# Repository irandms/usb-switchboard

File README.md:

# USB Switchboard Bonnet

This repository houses the KiCad design files for a Raspberry Pi Zero Bonnet
board. The system provides three independently controlled USB ports, which can
be selectively enabled or disabled for power delivery purposes via 3 GPIO pins
on the Pi host. The data pins for all receptacles are unused.

In addition to being able to digitally control each USB port, each port has
suppport for overcurrent protection via the [Texas Instruments TPS2556 IC](https://www.ti.com/product/TPS2556)
, capping out to ~500 mA per port. Fault/short circuit and temperature 
protection is also provided by the TPS2556.

When tested using an Pac-Man Silhouette LED Blue Ghost, it can provide PWM 
diming at ~500 Hz or faster depending on the period, with an untested upper
bound.

The initial set of prototype boards were made at [OSH Park](https://oshpark.com/shared_projects/6m9zgemo) using their 2oz Copper service, as the current through
the 5V input net from the Pi host could be fairly high depending on the
state of each of the ports and the devices connected to them.

bill-of-materials.csv contains a DigiKey-importable Bill of Materials that
has every component required on the PCB. Notably missing are the HAT EEPROM and
related passives, which can be found on the underside of the board.

The three channels can be enabled/disabled through the following GPIO pins:

| GPIO Pin      | Channel       |
| ------------- |:-------------:|
| GPIO2         | CH0           |
| GPIO10        | CH1           |
| GPIO11        | CH2           |

## NOTE:
I have not worked on including an EEPROM for this board to conform to the 
official Raspberry Pi Bonnet/HAT spec.

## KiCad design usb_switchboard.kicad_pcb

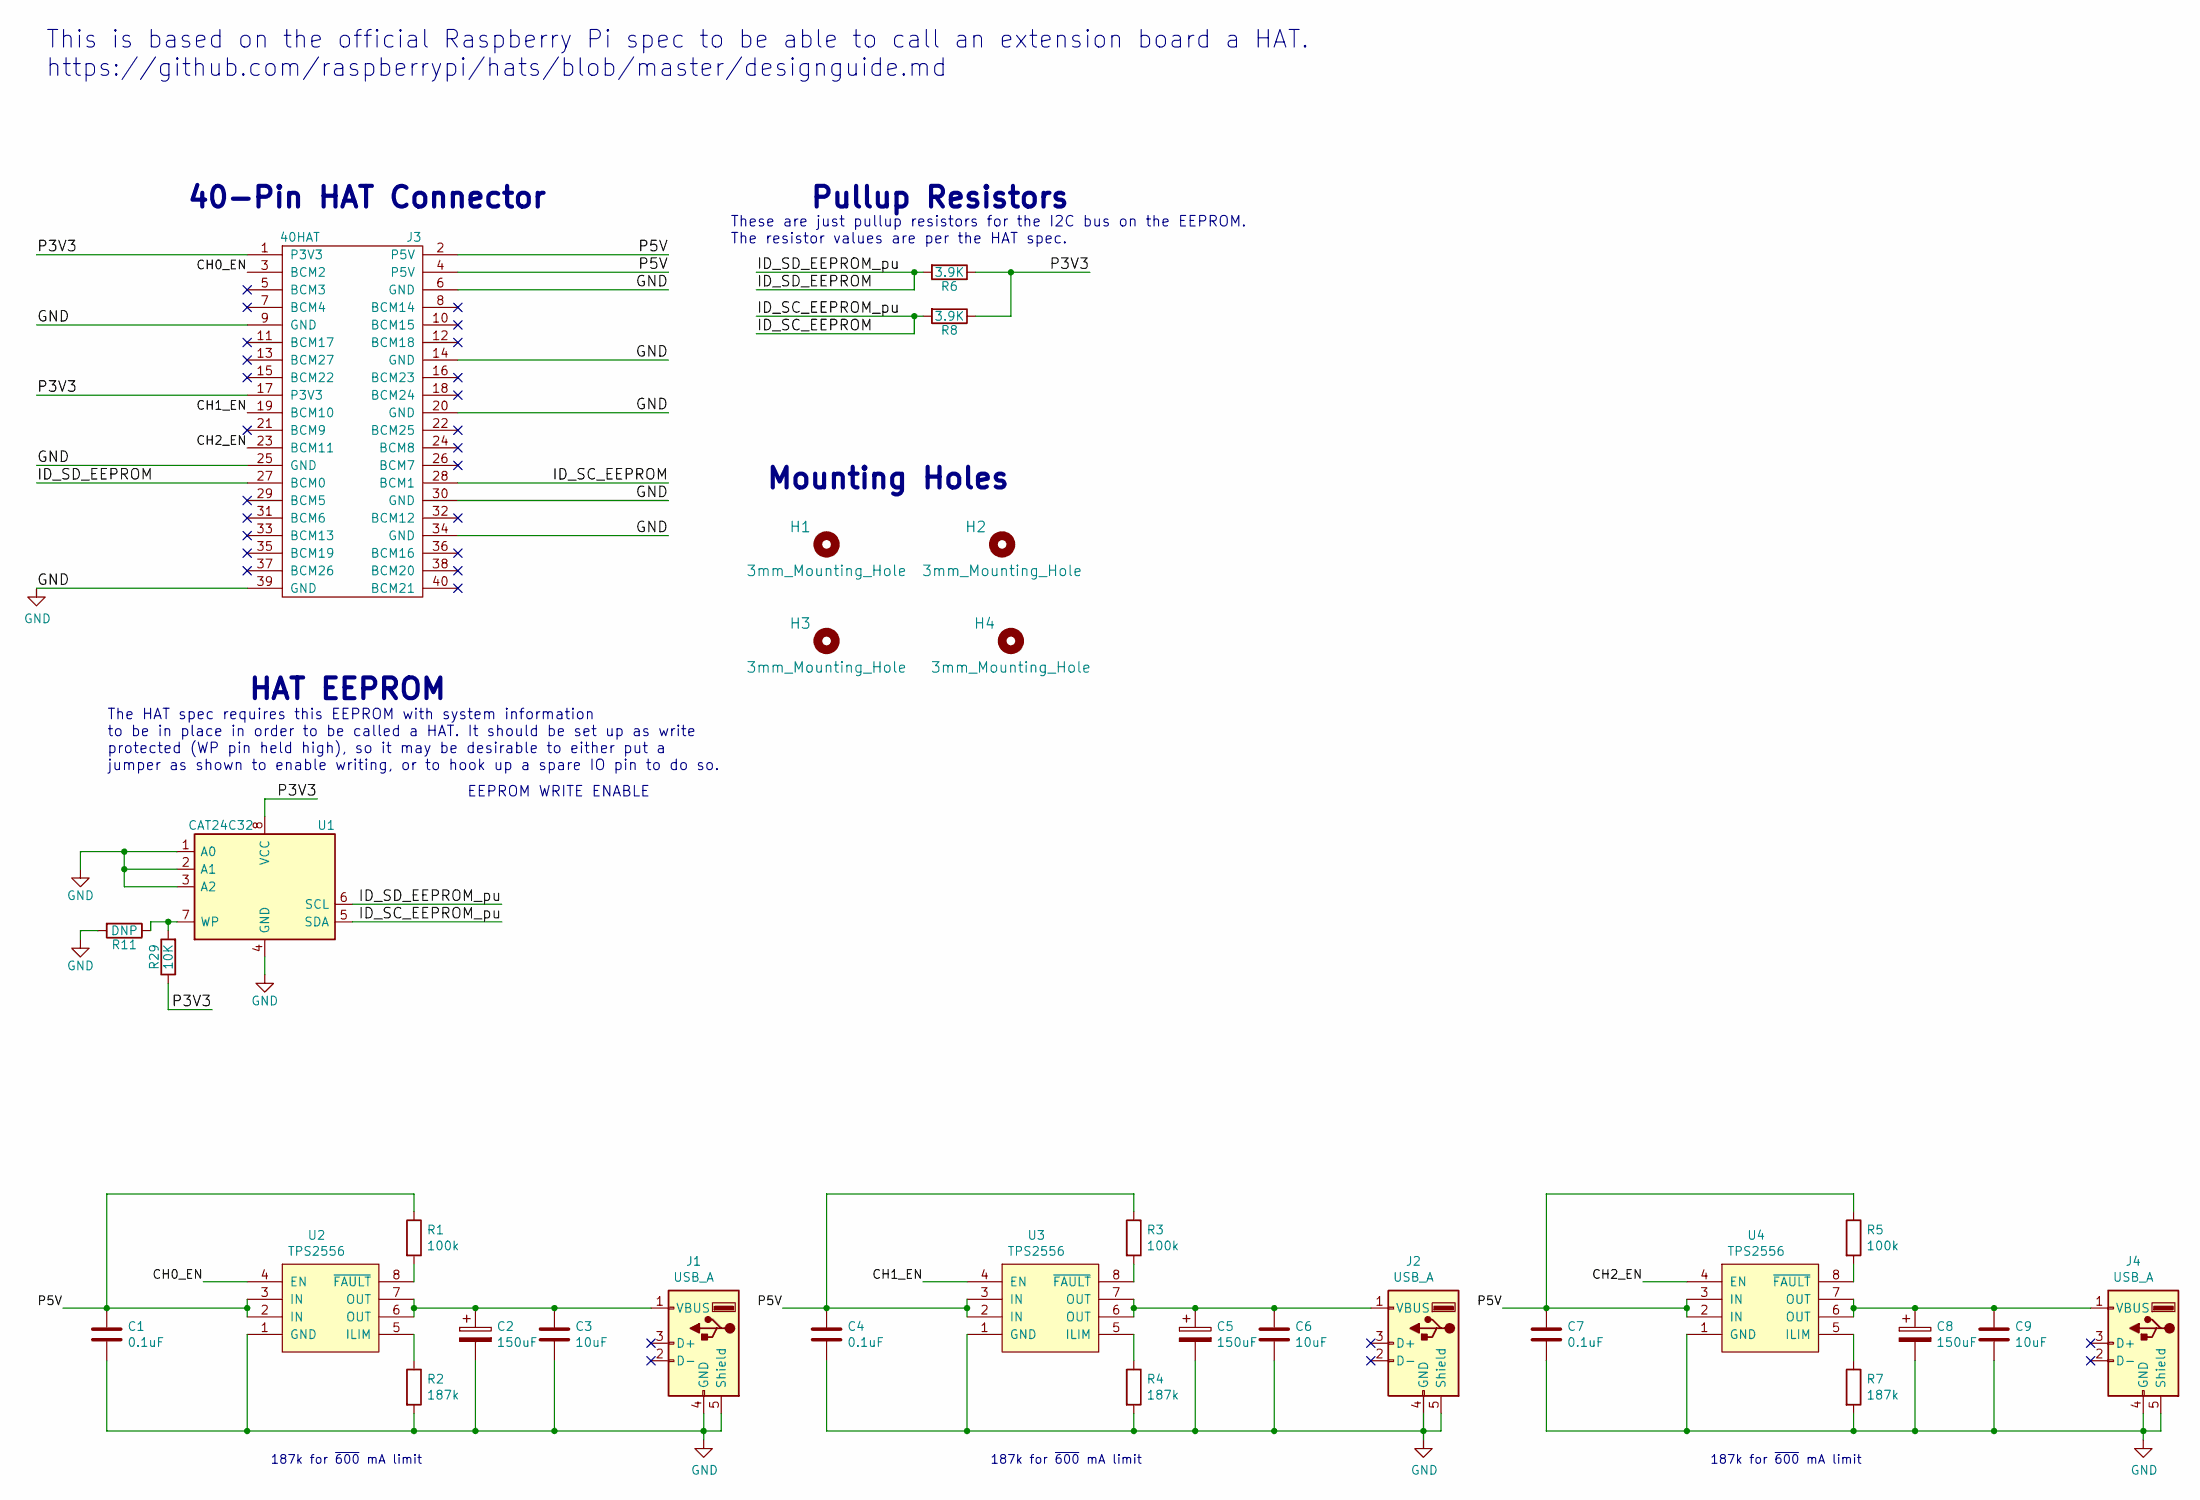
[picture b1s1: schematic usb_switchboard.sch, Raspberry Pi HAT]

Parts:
C1, C4, C7: 0.1uF; C_0603_1608Metric
C2, C5, C8: 150uF; CP_Elec_5x5.3
C3, C6, C9: 10uF; R_0603_1608Metric
H1, H2, H3, H4: 3mm_Mounting_Hole; NPTH_3mm_ID
J1, J2, J4: USB_A; USB3_A_Molex_48393-001
J3: 40HAT; PinSocket_2x20_P2.54mm_Vertical
R1, R3, R5: 100k; R_0603_1608Metric
R2, R4, R7: 187k; R_0603_1608Metric
R6, R8: 3.9K; R_0603_1608Metric_Pad0.84x1.00mm_HandSolder
R11: DNP; R_0603_1608Metric_Pad0.84x1.00mm_HandSolder
R29: 10K; R_0603_1608Metric_Pad0.84x1.00mm_HandSolder
U1: CAT24C32; SOIC-8_3.9x4.9mm_P1.27mm
U2, U3, U4: TPS2556; Texas_S-PVSON-N8_ThermalVias

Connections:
/CH0_EN: J3.3 (BCM2), U2.4 (EN)
/CH1_EN: J3.19 (BCM10), U3.4 (EN)
/CH2_EN: J3.23 (BCM11), U4.4 (EN)
/ID_SC_EEPROM: J3.28 (BCM1), R8.2, U1.5 (SDA)
/ID_SD_EEPROM: J3.27 (BCM0), R6.2, U1.6 (SCL)
/P3V3: J3.1 (P3V3), J3.17 (P3V3), R6.1, R8.1, R29.1, U1.8 (VCC)
/P5V: C1.1, C4.1, C7.1, J3.2 (P5V), J3.4 (P5V), R1.1, R3.1, R5.1, U2.2 (IN), U2.3 (IN), U3.2 (IN), U3.3 (IN), U4.2 (IN), U4.3 (IN)
GND: C1.2, C2.2, C3.2, C4.2, C5.2, C6.2, C7.2, C8.2, C9.2, J1.4 (GND), J1.5 (Shield), J2.4 (GND), J2.5 (Shield), J3.6 (GND), J3.9 (GND), J3.14 (GND), J3.20 (GND), J3.25 (GND), J3.30 (GND), J3.34 (GND), J3.39 (GND), J4.4 (GND), J4.5 (Shield), R2.2, R4.2, R7.2, R11.2, U1.1 (A0), U1.2 (A1), U1.3 (A2), U1.4 (GND), U2.1 (GND), U2.9 (PAD), U3.1 (GND), U3.9 (PAD), U4.1 (GND), U4.9 (PAD); also elsewhere on the board
unnamed 8: C2.1, C3.1, J1.1 (VBUS), U2.6 (OUT), U2.7 (OUT); also elsewhere on the board
unnamed 9: C5.1, C6.1, J2.1 (VBUS), U3.6 (OUT), U3.7 (OUT); also elsewhere on the board
unnamed 10: C8.1, C9.1, J4.1 (VBUS), U4.6 (OUT), U4.7 (OUT); also elsewhere on the board
unnamed: R1.2, U2.8 (~FAULT)
unnamed: R2.1, U2.5 (ILIM)
unnamed: R3.2, U3.8 (~FAULT)
unnamed: R4.1, U3.5 (ILIM)
unnamed: R5.2, U4.8 (~FAULT)
unnamed: R7.1, U4.5 (ILIM)
unnamed: R11.1, R29.2, U1.7 (WP)

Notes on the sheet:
EEPROM WRITE ENABLE
Pullup Resistors
HAT EEPROM
Mounting Holes
40-Pin HAT Connector
The HAT spec requires this EEPROM with system information to be in place in order to be called a HAT. It should be set up as write protected (WP pin held high), so it may be desirable to either put a jumper as shown to enable writing, or to hook up a spare IO pin to do so.
These are just pullup resistors for the I2C bus on the EEPROM. The resistor values are per the HAT spec.
This is based on the official Raspberry Pi spec to be able to call an extension board a HAT. https://github.com/raspberrypi/hats/blob/master/designguide.md
187k for ~600 mA limit

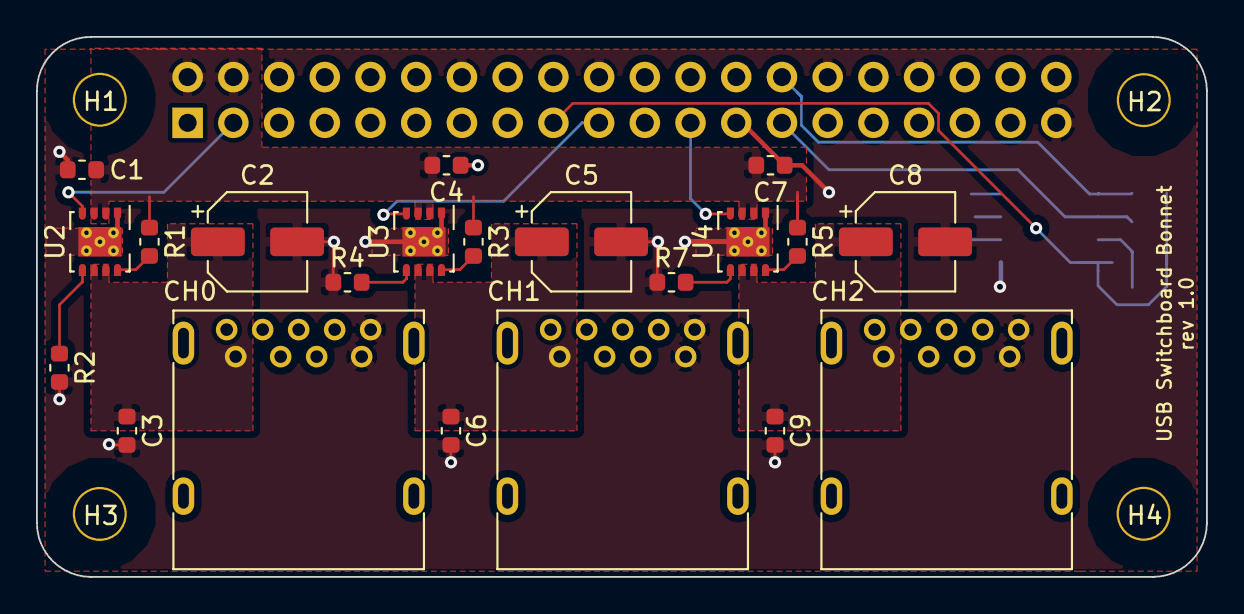
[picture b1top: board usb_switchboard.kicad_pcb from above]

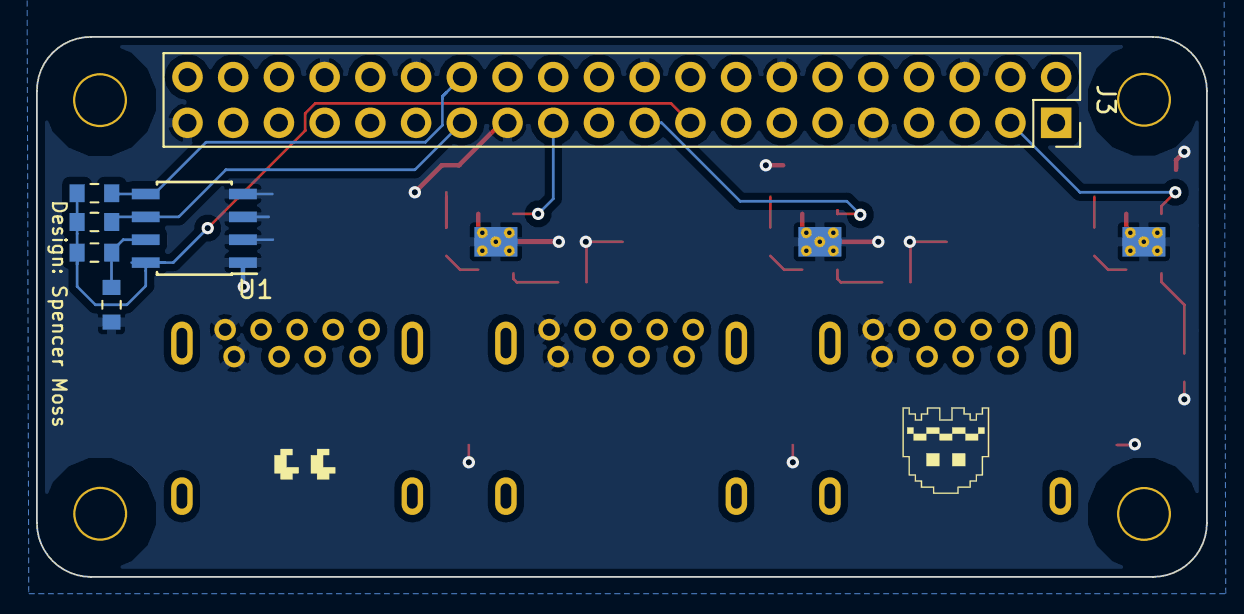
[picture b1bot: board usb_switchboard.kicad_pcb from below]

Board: 2 copper layers, 65.0 x 30.0 mm, 31 parts (6 on the bottom side), 18 nets.

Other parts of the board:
CH0, CH1, CH2: USB_A; USB3_A_Molex_48393-001

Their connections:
GND: CH0.4, CH0.5, CH1.4, CH1.5, CH2.4, CH2.5; also elsewhere on the board
unnamed 8: CH0.1; also elsewhere on the board
unnamed 9: CH1.1; also elsewhere on the board
unnamed 10: CH2.1; also elsewhere on the board

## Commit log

2019-06-10 Finished rev 1.0
2019-06-10 Add schematic PDF
2019-06-16 Updated README and added BoM
2019-07-03 Add image to README.md
